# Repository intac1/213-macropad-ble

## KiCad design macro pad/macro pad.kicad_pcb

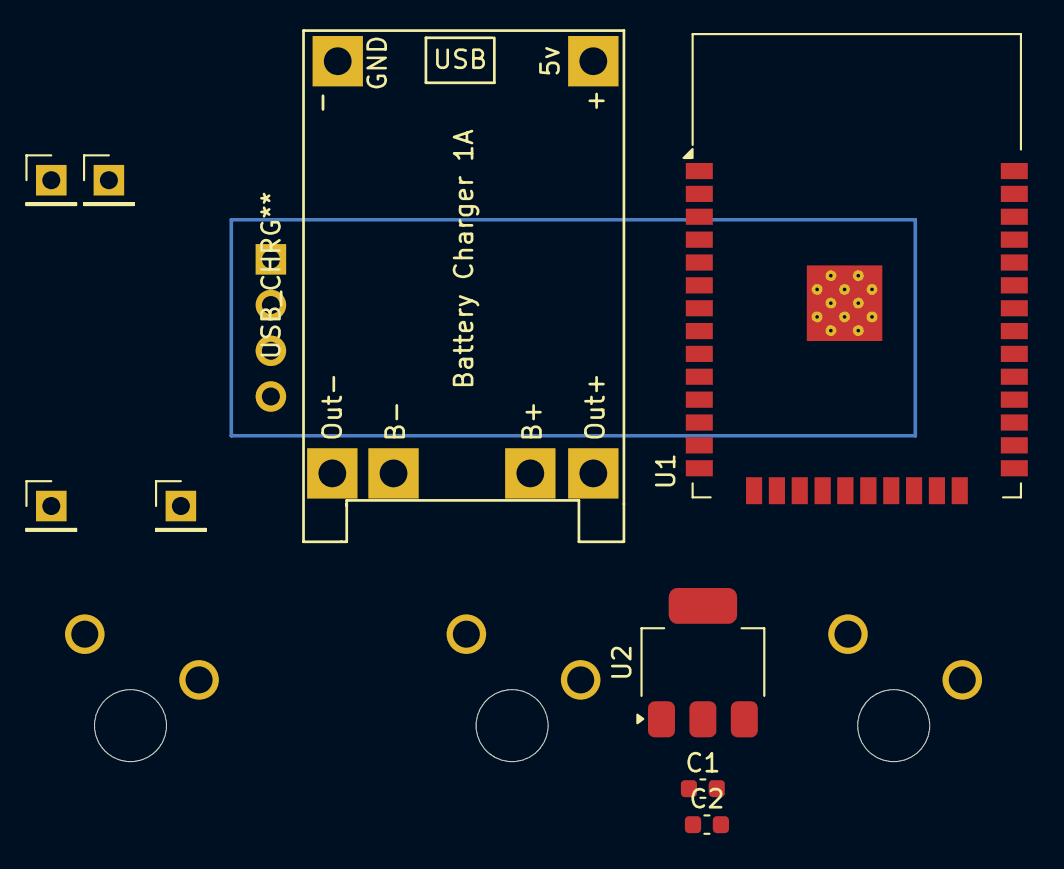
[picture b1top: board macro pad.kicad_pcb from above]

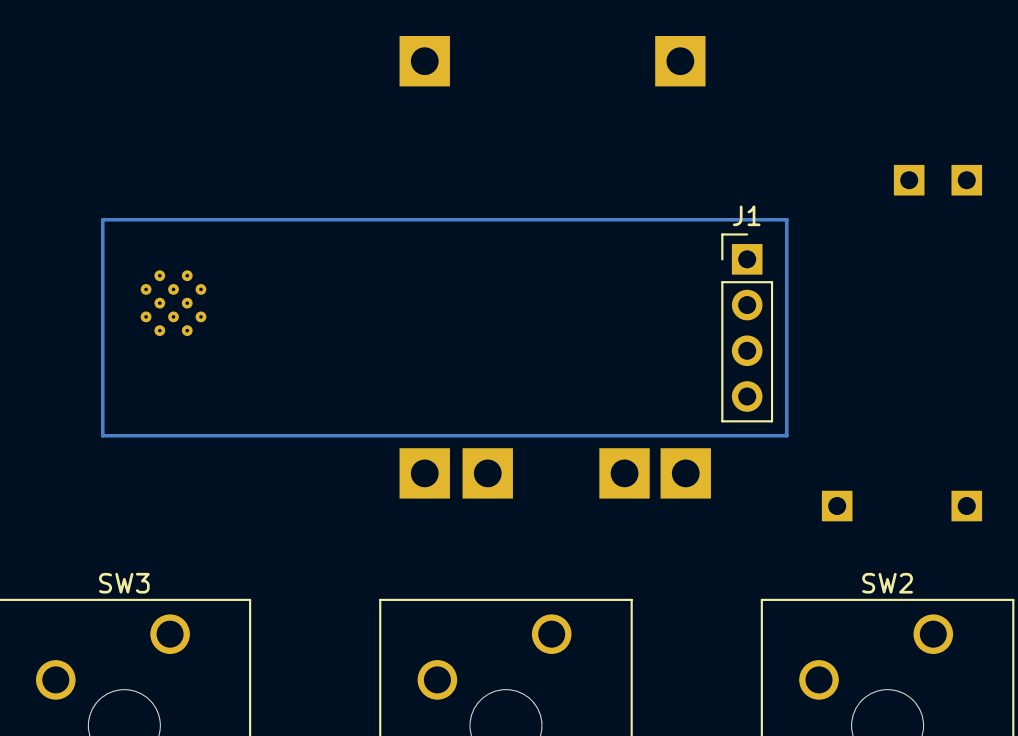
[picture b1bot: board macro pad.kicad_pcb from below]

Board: 2 copper layers, 13 parts (4 on the bottom side), 3 nets, no tracks yet.

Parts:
5V1: PinHeader_1x01_P2.54mm_Vertical
C1, C2: C; C_0603_1608Metric
GND1, GND2: PinHeader_1x01_P2.54mm_Vertical
J1: Conn_01x04_Pin; PinHeader_1x04_P2.54mm_Vertical
SW1, SW2, SW3: SW_Push; SW_Cherry_MX_1.00u_Plate
U1: ESP32-WROOM-32
U2: AMS1117-3.3; SOT-223-3_TabPin2
USB_CHRG**: TP4056-18650
VBAT1: PinHeader_1x01_P2.54mm_Vertical

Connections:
unnamed: U1.1 (GND), U1.15 (GND), U1.38 (GND), U1.39 (GND)
SCK: J1.3, U1.30 (IO18)
SDA: J1.4, U1.31 (IO19)
